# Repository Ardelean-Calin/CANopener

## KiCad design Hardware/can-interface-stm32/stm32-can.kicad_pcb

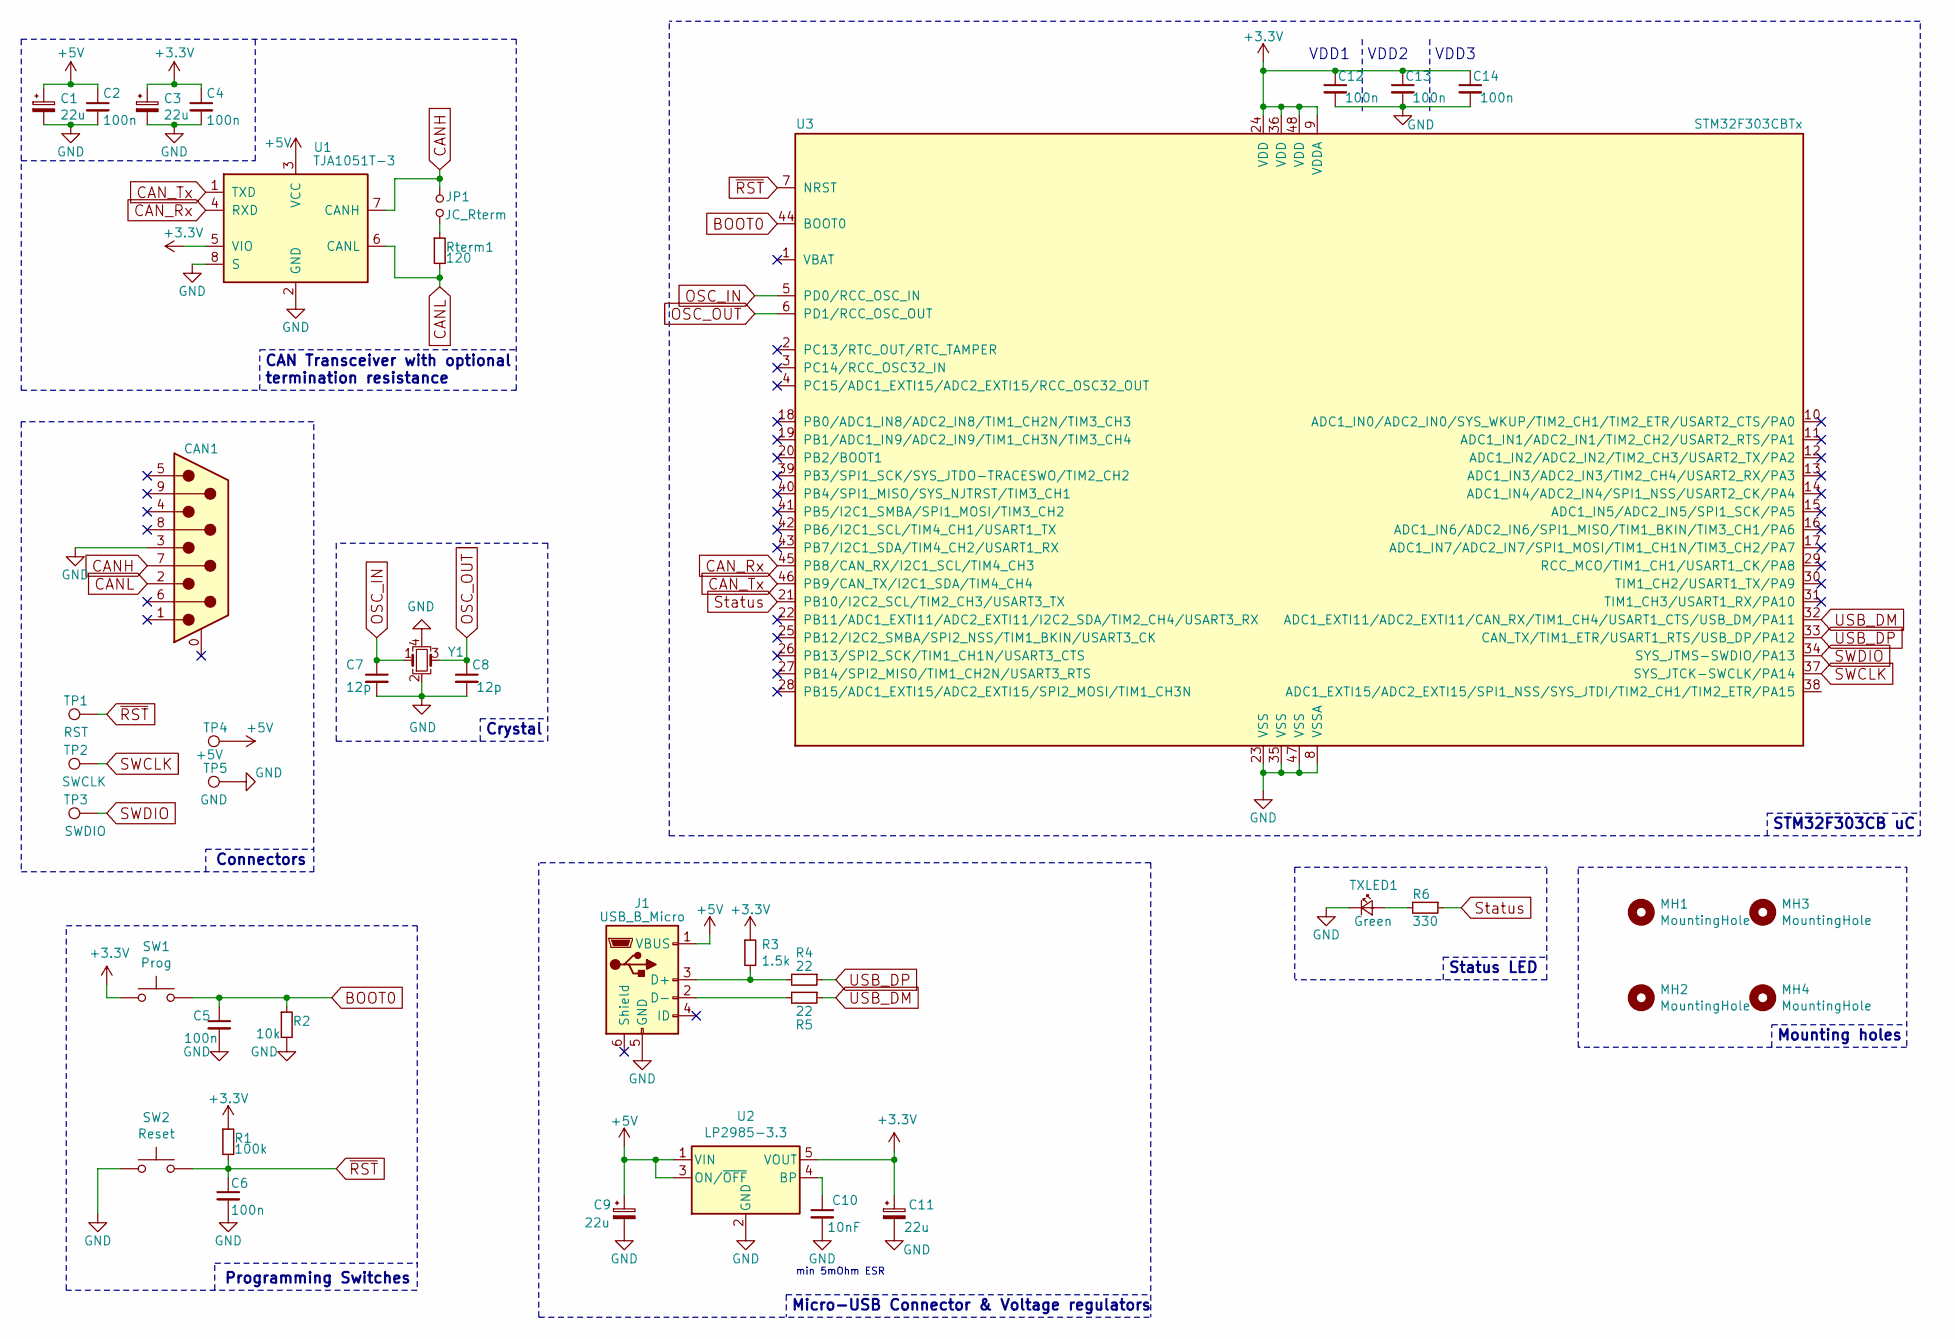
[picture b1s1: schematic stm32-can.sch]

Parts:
C1, C3, C9, C11: 22u; C_0805_HandSoldering
C2, C4, C5, C6, C12, C13, C14: 100n; C_0603_HandSoldering
C7, C8: 12p; C_0603_HandSoldering
C10: 10nF; C_0603_HandSoldering
CAN1: CAN_Connector; DSUB-9_Male_Horizontal_P2.77x2.84mm_EdgePinOffset4.94mm_Hou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
J1: USB_B_Micro; USB_Micro-B_Wuerth-629105150521_CircularHoles
JP1: JC_Rterm; Pin_Header_Straight_1x02_Pitch2.54mm
MH1, MH2, MH3, MH4: MountingHole; MountingHole_2.2mm_M2_ISO14580_Pad
R1: 100k; R_0603_HandSoldering
R2: 10k; R_0603_HandSoldering
R3: 1.5k; R_0603_HandSoldering
R4, R5: 22; R_0603_HandSoldering
R6: 330; R_0603_HandSoldering
Rterm1: 120; R_0603_HandSoldering
SW1: Prog; SW_SPST_FSMSM
SW2: Reset; SW_SPST_FSMSM
TP1: RST; Measurement_Point_Round-SMD-Pad_Small
TP2: SWCLK; Measurement_Point_Round-SMD-Pad_Small
TP3: SWDIO; Measurement_Point_Round-SMD-Pad_Small
TP4: +5V; Measurement_Point_Round-SMD-Pad_Small
TP5: GND; Measurement_Point_Round-SMD-Pad_Small
TXLED1: Green; LED_0603_HandSoldering
U1: TJA1051T-3; SOIC-8_3.9x4.9mm_Pitch1.27mm
U2: LP2985-3.3; SOT-23-5_HandSoldering
U3: STM32F303CBTx; LQFP-48_7x7mm_Pitch0.5mm
Y1: Crystal_GND24_Small; Crystal_SMD_3225-4pin_3.2x2.5mm_HandSoldering

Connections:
+3V3: C3.1, C4.1, C11.1, C12.1, C13.1, C14.1, R1.1, R3.1, SW1.1, U1.5 (VIO), U2.5 (VOUT), U3.9 (VDDA), U3.24 (VDD), U3.36 (VDD), U3.48 (VDD)
+5V: C1.1, C2.1, C9.1, J1.1 (VBUS), TP4.1, U1.3 (VCC), U2.1 (VIN), U2.3 (ON/~OFF~)
BOOT0: C5.1, R2.1, SW1.2, U3.44 (BOOT0)
CANH: CAN1.7, JP1.2, U1.7 (CANH)
CANL: CAN1.2, Rterm1.2, U1.6 (CANL)
CAN_Rx: U1.4 (RXD), U3.45 (PB8/CAN_RX/I2C1_SCL/TIM4_CH3)
CAN_Tx: U1.1 (TXD), U3.46 (PB9/CAN_TX/I2C1_SDA/TIM4_CH4)
GND: C1.2, C2.2, C3.2, C4.2, C5.2, C6.2, C7.2, C8.2, C9.2, C10.2, C11.2, C12.2, C13.2, C14.2, CAN1.3, J1.5 (GND), R2.2, SW2.1, TP5.1, TXLED1.1 (K), U1.2 (GND), U1.8 (S), U2.2 (GND), U3.8 (VSSA), U3.23 (VSS), U3.35 (VSS), U3.47 (VSS), Y1.2, Y1.4
unnamed: C10.1, U2.4 (BP)
unnamed: J1.2 (D-), R5.2
unnamed: J1.3 (D+), R3.2, R4.2
unnamed: JP1.1, Rterm1.1
unnamed: R6.2, TXLED1.2 (A)
OSC_IN: C7.1, U3.5 (PD0/RCC_OSC_IN), Y1.1
OSC_OUT: C8.1, U3.6 (PD1/RCC_OSC_OUT), Y1.3
SWCLK: TP2.1, U3.37 (SYS_JTCK-SWCLK/PA14)
SWDIO: TP3.1, U3.34 (SYS_JTMS-SWDIO/PA13)
Status: R6.1, U3.21 (PB10/I2C2_SCL/TIM2_CH3/USART3_TX)
USB_DM: R5.1, U3.32 (ADC1_EXTI11/ADC2_EXTI11/CAN_RX/TIM1_CH4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)
USB_DP: R4.1, U3.33 (CAN_TX/TIM1_ETR/USART1_RTS/USB_DP/PA12)
~RST: C6.1, R1.2, SW2.2, TP1.1, U3.7 (NRST)

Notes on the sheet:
VDD1
VDD2
VDD3
Micro-USB Connector & Voltage regulators
CAN Transceiver with optional termination resistance
Status LED
Connectors
STM32F303CB uC
min 5mOhm ESR
Mounting holes
Programming Switches
Crystal

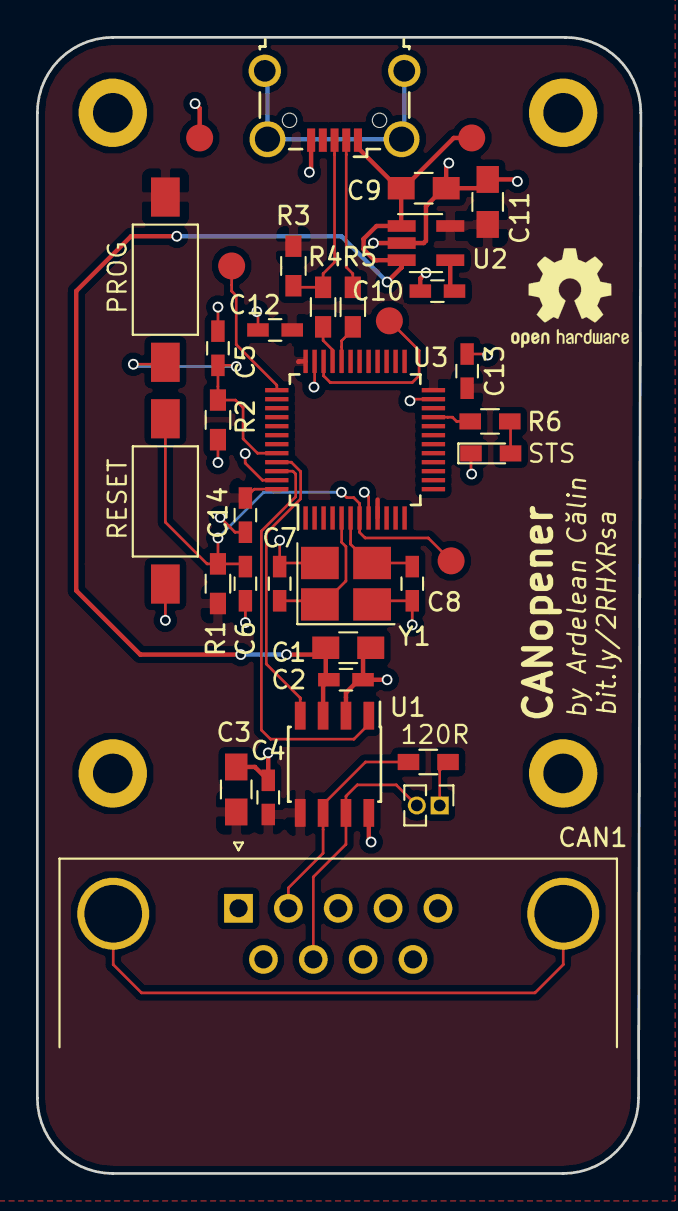
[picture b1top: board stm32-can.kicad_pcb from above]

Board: 2 copper layers, 33.5 x 63.1 mm, 40 parts (0 on the bottom side), 21 nets.

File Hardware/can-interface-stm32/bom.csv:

"Source:","C:\Users\Ardelean Calin\OneDrive\Hardware & Programming\can-interface-stm32\stm32-can.sch"
"Date:","07-Nov-18 9:48:11 PM"
"Tool:","Eeschema (5.0.1)-3"
"Generator:","C:\Users\Ardelean Calin\scoop\apps\kicad\current\bin\scripting\plugins/bom_csv_grouped_by_value.py"
"Component Count:","35"

"Individual Components:"

"Item","Qty","Reference(s)","Value","LibPart","Footprint","Datasheet"
"","","C1","22u","stm32-can-rescue:CP_Small-Device","Capacitors_SMD:C_0805_HandSoldering","~"
"","","C2","100n","stm32-can-rescue:C_Small-Device","Capacitors_SMD:C_0603_HandSoldering","~"
"","","C3","22u","stm32-can-rescue:CP_Small-Device","Capacitors_SMD:C_0805_HandSoldering","~"
"","","C4","100n","stm32-can-rescue:C_Small-Device","Capacitors_SMD:C_0603_HandSoldering","~"
"","","C5","100n","stm32-can-rescue:C_Small-Device","Capacitors_SMD:C_0603_HandSoldering",""
"","","C6","100n","stm32-can-rescue:C_Small-Device","Capacitors_SMD:C_0603_HandSoldering",""
"","","C7","12p","stm32-can-rescue:C_Small-Device","Capacitors_SMD:C_0603_HandSoldering","~"
"","","C8","12p","stm32-can-rescue:C_Small-Device","Capacitors_SMD:C_0603_HandSoldering","~"
"","","C9","22u","stm32-can-rescue:CP_Small-Device","Capacitors_SMD:C_0805_HandSoldering","~"
"","","C10","10nF","stm32-can-rescue:C_Small-Device","Capacitors_SMD:C_0603_HandSoldering","~"
"","","C11","22u","stm32-can-rescue:CP_Small-Device","Capacitors_SMD:C_0805_HandSoldering","~"
"","","C12","100n","stm32-can-rescue:C_Small-Device","Capacitors_SMD:C_0603_HandSoldering",""
"","","C13","100n","stm32-can-rescue:C_Small-Device","Capacitors_SMD:C_0603_HandSoldering",""
"","","C14","100n","stm32-can-rescue:C_Small-Device","Capacitors_SMD:C_0603_HandSoldering",""
"","","CAN1","CAN_Connector","stm32-can-rescue:DB9_Male_MountingHoles","library:DSUB-9_Male_Horizontal_P2.77x2.84mm_EdgePinOffset4.94mm_Housed_MountingHolesOffset7.48mm",""
"","","J1","USB_B_Micro","stm32-can-rescue:USB_B_Micro-Connector","Connectors_USB:USB_Micro-B_Wuerth-629105150521_CircularHoles","~"
"","","JP1","JC_Rterm","stm32-can-rescue:Jumper_NO_Small-Device","Pin_Headers:Pin_Header_Straight_1x02_Pitch2.54mm",""
"","","MH1","MountingHole","stm32-can-rescue:MountingHole-Mechanical","Mounting_Holes:MountingHole_2.2mm_M2_ISO14580_Pad","~"
"","","MH2","MountingHole","stm32-can-rescue:MountingHole-Mechanical","Mounting_Holes:MountingHole_2.2mm_M2_ISO14580_Pad","~"
"","","MH3","MountingHole","stm32-can-rescue:MountingHole-Mechanical","Mounting_Holes:MountingHole_2.2mm_M2_ISO14580_Pad","~"
"","","MH4","MountingHole","stm32-can-rescue:MountingHole-Mechanical","Mounting_Holes:MountingHole_2.2mm_M2_ISO14580_Pad","~"
"","","R1","100k","stm32-can-rescue:R_Small-Device","Resistors_SMD:R_0603_HandSoldering",""
"","","R2","10k","stm32-can-rescue:R_Small-Device","Resistors_SMD:R_0603_HandSoldering",""
"","","R3","1.5k","stm32-can-rescue:R_Small-Device","Resistors_SMD:R_0603_HandSoldering","~"
"","","R4","22","stm32-can-rescue:R_Small-Device","Resistors_SMD:R_0603_HandSoldering","~"
"","","R5","22","stm32-can-rescue:R_Small-Device","Resistors_SMD:R_0603_HandSoldering","~"
"","","R6","330","stm32-can-rescue:R_Small-Device","Resistors_SMD:R_0603_HandSoldering",""
"","","Rterm1","120","stm32-can-rescue:R_Small-Device","Resistors_SMD:R_0603_HandSoldering",""
"","","SW1","Prog","stm32-can-rescue:SW_Push-Switch","Buttons_Switches_SMD:SW_SPST_FSMSM",""
"","","SW2","Reset","stm32-can-rescue:SW_Push-Switch","Buttons_Switches_SMD:SW_SPST_FSMSM",""
"","","TXLED1","Green","stm32-can-rescue:LED_Small-Device","LEDs:LED_0603_HandSoldering",""
"","","U1","TJA1051T-3","stm32-can-rescue:TJA1051T-3-Interface_CAN_LIN","Housings_SOIC:SOIC-8_3.9x4.9mm_Pitch1.27mm","http://www.nxp.com/documents/data_sheet/TJA1051.pdf"
"","","U2","LP2985-3.3","stm32-can-rescue:LP2985-3.3-Regulator_Linear","TO_SOT_Packages_SMD:SOT-23-5_HandSoldering","http://www.ti.com/lit/ds/symlink/lp2985.pdf"
"","","U3","STM32F303CBTx","stm32-can-rescue:STM32F103CBTx","Housings_QFP:LQFP-48_7x7mm_Pitch0.5mm",""
"","","Y1","Crystal_GND24_Small","stm32-can-rescue:Crystal_GND24_Small-Device","Crystals:Crystal_SMD_3225-4pin_3.2x2.5mm_HandSoldering","~"



"Collated Components:"

"Item","Qty","Reference(s)","Value","LibPart","Footprint","Datasheet"
"1","4","C1, C3, C9, C11","22u","stm32-can-rescue:CP_Small-Device","Capacitors_SMD:C_0805_HandSoldering","~"
"2","7","C2, C4, C5, C6, C12, C13, C14","100n","stm32-can-rescue:C_Small-Device","Capacitors_SMD:C_0603_HandSoldering","~"
"3","2","C7, C8","12p","stm32-can-rescue:C_Small-Device","Capacitors_SMD:C_0603_HandSoldering","~"
"4","1","C10","10nF","stm32-can-rescue:C_Small-Device","Capacitors_SMD:C_0603_HandSoldering","~"
"5","1","CAN1","CAN_Connector","stm32-can-rescue:DB9_Male_MountingHoles","library:DSUB-9_Male_Horizontal_P2.77x2.84mm_EdgePinOffset4.94mm_Housed_MountingHolesOffset7.48mm",""
"6","1","J1","USB_B_Micro","stm32-can-rescue:USB_B_Micro-Connector","Connectors_USB:USB_Micro-B_Wuerth-629105150521_CircularHoles","~"
"7","1","JP1","JC_Rterm","stm32-can-rescue:Jumper_NO_Small-Device","Pin_Headers:Pin_Header_Straight_1x02_Pitch2.54mm",""
"8","4","MH1, MH2, MH3, MH4","MountingHole","stm32-can-rescue:MountingHole-Mechanical","Mounting_Holes:MountingHole_2.2mm_M2_ISO14580_Pad","~"
"9","1","R1","100k","stm32-can-rescue:R_Small-Device","Resistors_SMD:R_0603_HandSoldering",""
"10","1","R2","10k","stm32-can-rescue:R_Small-Device","Resistors_SMD:R_0603_HandSoldering",""
"11","1","R3","1.5k","stm32-can-rescue:R_Small-Device","Resistors_SMD:R_0603_HandSoldering","~"
"12","2","R4, R5","22","stm32-can-rescue:R_Small-Device","Resistors_SMD:R_0603_HandSoldering","~"
"13","1","R6","330","stm32-can-rescue:R_Small-Device","Resistors_SMD:R_0603_HandSoldering",""
"14","1","Rterm1","120","stm32-can-rescue:R_Small-Device","Resistors_SMD:R_0603_HandSoldering",""
"15","1","SW1","Prog","stm32-can-rescue:SW_Push-Switch","Buttons_Switches_SMD:SW_SPST_FSMSM",""
"16","1","SW2","Reset","stm32-can-rescue:SW_Push-Switch","Buttons_Switches_SMD:SW_SPST_FSMSM",""
"17","1","TXLED1","Green","stm32-can-rescue:LED_Small-Device","LEDs:LED_0603_HandSoldering",""
"18","1","U1","TJA1051T-3","stm32-can-rescue:TJA1051T-3-Interface_CAN_LIN","Housings_SOIC:SOIC-8_3.9x4.9mm_Pitch1.27mm","http://www.nxp.com/documents/data_sheet/TJA1051.pdf"
"19","1","U2","LP2985-3.3","stm32-can-rescue:LP2985-3.3-Regulator_Linear","TO_SOT_Packages_SMD:SOT-23-5_HandSoldering","http://www.ti.com/lit/ds/symlink/lp2985.pdf"
"20","1","U3","STM32F303CBTx","stm32-can-rescue:STM32F103CBTx","Housings_QFP:LQFP-48_7x7mm_Pitch0.5mm",""
"21","1","Y1","Crystal_GND24_Small","stm32-can-rescue:Crystal_GND24_Small-Device","Crystals:Crystal_SMD_3225-4pin_3.2x2.5mm_HandSoldering","~"

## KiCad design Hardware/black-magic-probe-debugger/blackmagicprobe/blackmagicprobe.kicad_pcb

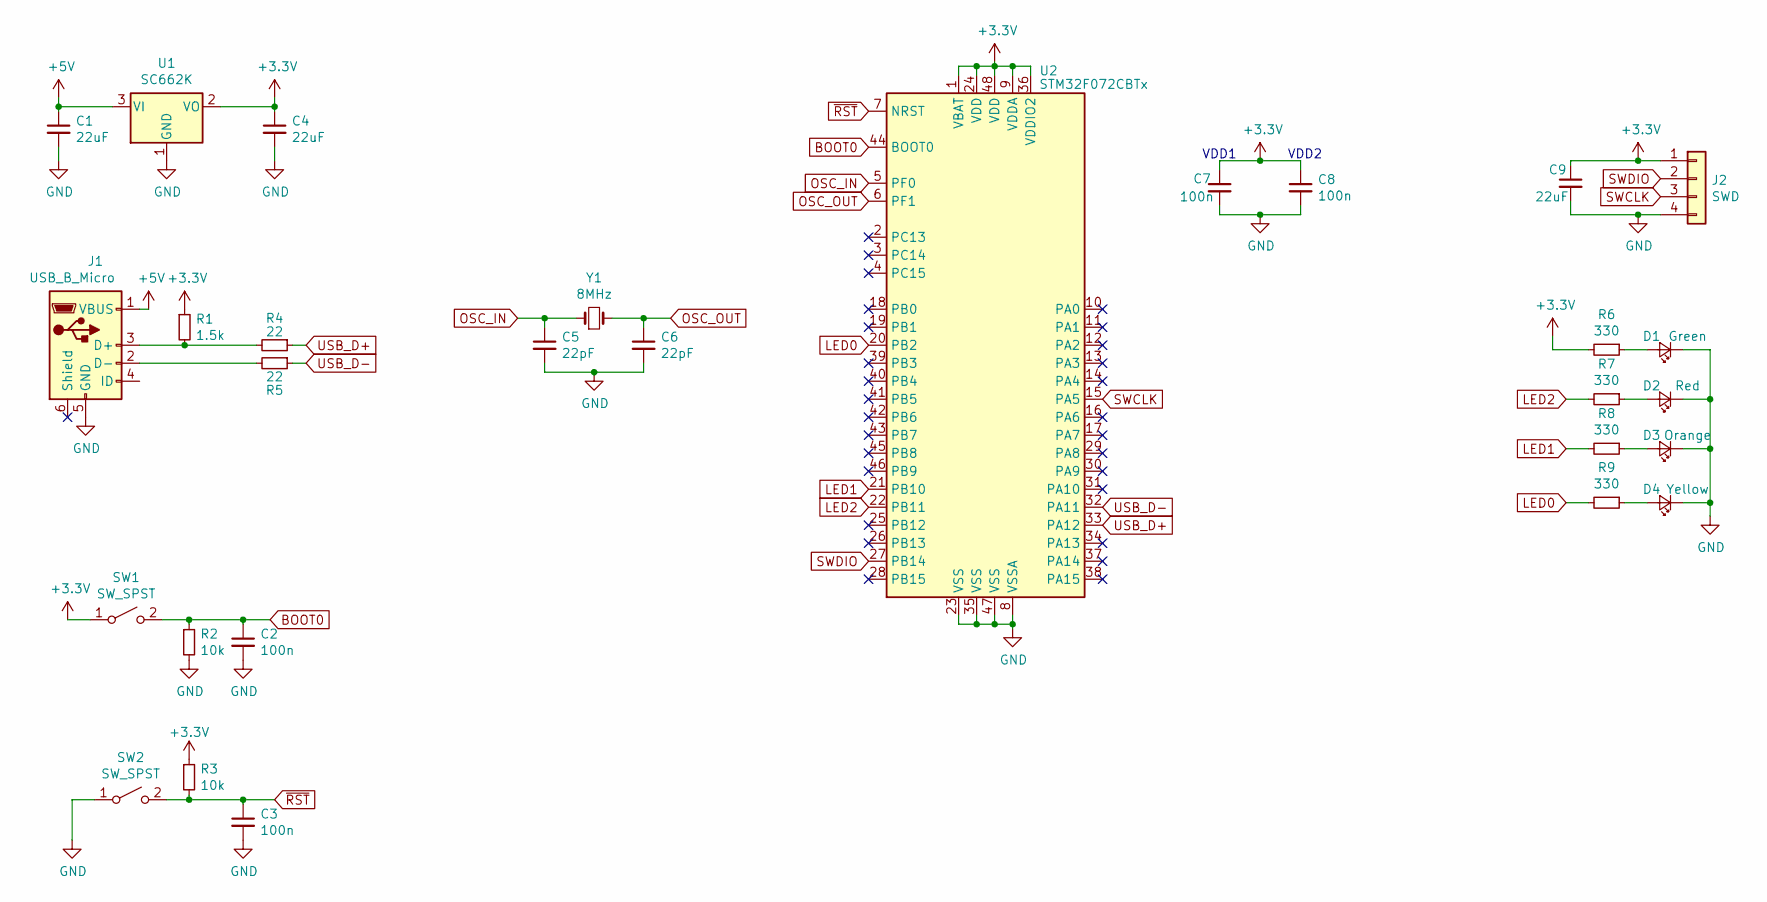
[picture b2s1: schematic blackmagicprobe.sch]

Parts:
C1, C4, C9: 22uF; C_0805
C2, C3, C7, C8: 100n; C_0603
C5, C6: 22pF; C_0603
D1: Green; LED_0603
D2: Red; LED_0603
D3: Orange; LED_0603
D4: Yellow; LED_0603
J1: USB_B_Micro; USB_Micro-B_Wuerth-629105150521
J2: SWD; Pin_Header_Angled_1x04_Pitch2.54mm
R1: 1.5k; R_0603
R2, R3: 10k; R_0603
R4, R5: 22; R_0603
R6, R7, R8, R9: 330; R_0603
SW1, SW2: SW_SPST; SW_SPST_B3U-3000P-B
U1: SC662K; SOT-23_Handsoldering
U2: STM32F072CBTx; LQFP-48_7x7mm_Pitch0.5mm
Y1: 8MHz; Crystal_SMD_5032-2pin_5.0x3.2mm

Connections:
+3V3: C4.1, C7.1, C8.1, C9.1, J2.1, R1.1, R3.1, R6.2, SW1.1 (A), U1.2 (VO), U2.1 (VBAT), U2.9 (VDDA), U2.24 (VDD), U2.36 (VDDIO2), U2.48 (VDD)
+5V: C1.1, J1.1 (VBUS), U1.3 (VI)
BOOT0: C2.1, R2.1, SW1.2 (B), U2.44 (BOOT0)
GND: C1.2, C2.2, C3.2, C4.2, C5.2, C6.2, C7.2, C8.2, C9.2, D1.1 (K), D2.1 (K), D3.1 (K), D4.1 (K), J1.5 (GND), J2.4, R2.2, SW2.1 (A), U1.1 (GND), U2.8 (VSSA), U2.23 (VSS), U2.35 (VSS), U2.47 (VSS)
LED0: R9.2, U2.20 (PB2)
LED1: R8.2, U2.21 (PB10)
LED2: R7.2, U2.22 (PB11)
unnamed: D1.2 (A), R6.1
unnamed: D2.2 (A), R7.1
unnamed: D3.2 (A), R8.1
unnamed: D4.2 (A), R9.1
unnamed: J1.2 (D-), R5.2
unnamed: J1.3 (D+), R1.2, R4.2
OSC_IN: C5.1, U2.5 (PF0), Y1.1
OSC_OUT: C6.1, U2.6 (PF1), Y1.2
SWCLK: J2.3, U2.15 (PA5)
SWDIO: J2.2, U2.27 (PB14)
USB_D+: R4.1, U2.33 (PA12)
USB_D-: R5.1, U2.32 (PA11)
~RST: C3.1, R3.2, SW2.2 (B), U2.7 (NRST)

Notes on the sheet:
VDD1
VDD2

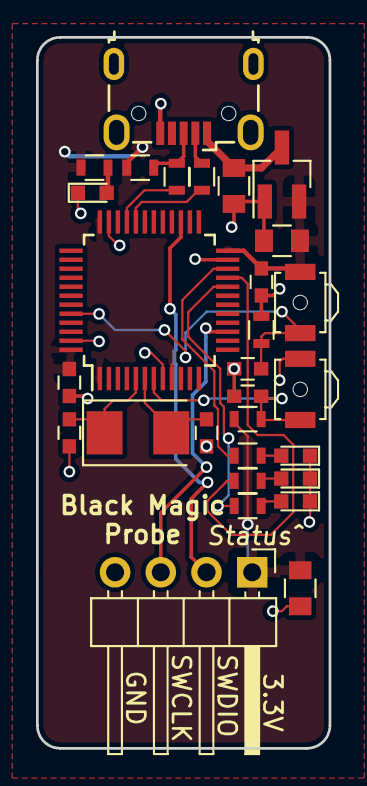
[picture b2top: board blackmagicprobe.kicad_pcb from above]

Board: 2 copper layers, 16.3 x 39.5 mm, 29 parts (0 on the bottom side), 20 nets.

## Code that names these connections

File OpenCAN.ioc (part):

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Mcu.Name=STM32F303C(B-C)Tx
Mcu.Package=LQFP48
Mcu.UserName=STM32F303CBTx
PA11.Mode=Device
PA11.Signal=USB_DM
PA12.Mode=Device
PA12.Signal=USB_DP
PA13.Mode=Serial_Wire
PA13.Signal=SYS_JTMS-SWDIO
PA14.Mode=Serial_Wire
PA14.Signal=SYS_JTCK-SWCLK
PB8.Mode=Master
PB8.Signal=CAN_RX
PB9.Mode=Master
PB9.Signal=CAN_TX
PF0-OSC_IN.Mode=HSE-External-Clock-Source
PF0-OSC_IN.Signal=RCC_OSC_IN
RCC.HSEPLLFreq_Value=8000000
RCC.HSE_VALUE=16000000
RCC.SYSCLKFreq_VALUE=72000000
RCC.SYSCLKSourceVirtual=RCC_SYSCLKSOURCE_PLLCLK
board=custom

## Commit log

2018-06-25 Initial commit. Working USB RX task
2018-09-19 Backup
2018-09-26 Added gitignore
2018-09-26 Removed Debug folder from .gitignore
2018-09-26 Working CAN receive
2018-09-27 Lowered per-function stack size.
2018-09-28 Backup before weekend. WIP towards CAN receive
2018-09-29 Just autoformat
2018-09-29 Incipient Makefile
2018-09-29 Makefile cleanup
2018-09-29 Further cleanup.
2018-09-29 Makefile cleanup & bugfix.
2018-09-29 Now completely able to debug using VSCode
2018-09-29 Small consistency improvement.
2018-09-29 Added debug tasks for VSCode.
2018-09-29 Removed Eclipse-related files.
2018-09-30 Now we won't break in startup.
2018-09-30 Automatic header language identification.
2018-09-30 Added COBS frame-encoding algorithm.
2018-09-30 FreeRTOS naming conventions.
2018-09-30 Switched to COBS frame-encoding algorithm.
2018-09-30 Switched to loopback mode for RX testing.
2018-10-01 Forcefully using bash as default shell
2018-10-01 Changed path of OpenOCD again. Really need to find a better solution
2018-10-01 Fixed typo. Am now able to debug Cortex Peripherals.
2018-10-01 Removed unused variable.
2018-10-01 Reformated TODO due to extension
2018-10-01 Removed absolute path of stlink config file
2018-10-01 Build does not depend on clean anymore.
2018-10-01 Removed unused OpenOCD config file
2018-10-01 Removed unused files
2018-10-15 Updated USB Dataframe format
2018-10-15 Switched to normal mode for CAN controller
2018-11-18 Added Acknowledge Request and Response
2018-11-18 Added .elf, .hex and .bin export
2018-11-18 Added Software Timer for Status LED & optimized priorities.
2018-11-19 Fixed priorities.
2018-11-19 Fixed make clean deleting all build folder
2018-11-19 Disabled software-timer for LED blinking; Using task
2018-11-19 Added size optimisation flags.
2018-11-20 Now separating code in different sections and dropping code that's not used.
2018-11-20 Disabled I2C HAL Driver
2018-11-20 Moved gc-sections options of linker.
2018-11-20 Cleaned up makefile.
2019-05-29 Added opencan-lib as submodule
2019-06-23 Added flashing capability using Black Magic Probe
2019-06-23 Updated settings.json
2019-06-30 Implemented baudrate change.
2019-06-30 Added BMP to launch.json
2019-06-30 Added WSL files to gitignore.
2019-06-30 Added peripheral states to gitignore and removed it from repo.
2019-07-07 Added WSL support.
2019-07-07 Updated opencan-lib
2019-07-07 Updated to latest opencan-lib
2019-07-07 Proper baudrate modification.
2019-07-08 Small improvements.
2019-07-09 Reassigned priorities
2019-07-09 Added flashing task
2019-07-11 Named enums
2019-07-11 Adapted priorities again.
2019-07-11 VSCode settings
2019-07-11 Added trace of sending and receiving a CAN mesage.
2019-07-11 Added tracealyzer trace recording in DEBUG mode
2019-07-12 Fixed tracing
2019-07-12 Added DEBUG define
2019-07-13 Maybe better interrupt handling.
2019-07-17 adapted priorities
2019-07-17 Disertatia predata
